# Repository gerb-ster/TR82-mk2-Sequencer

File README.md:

# TR82 mk2 'sequencer'

A 16-step sequencer for the TR82 mk2 drum computer.

## Status: Work in Progress

- done: first schematic & board design
- todo: breadboard and test
- todo: design frontpanel
- todo: order PCB and build prototype

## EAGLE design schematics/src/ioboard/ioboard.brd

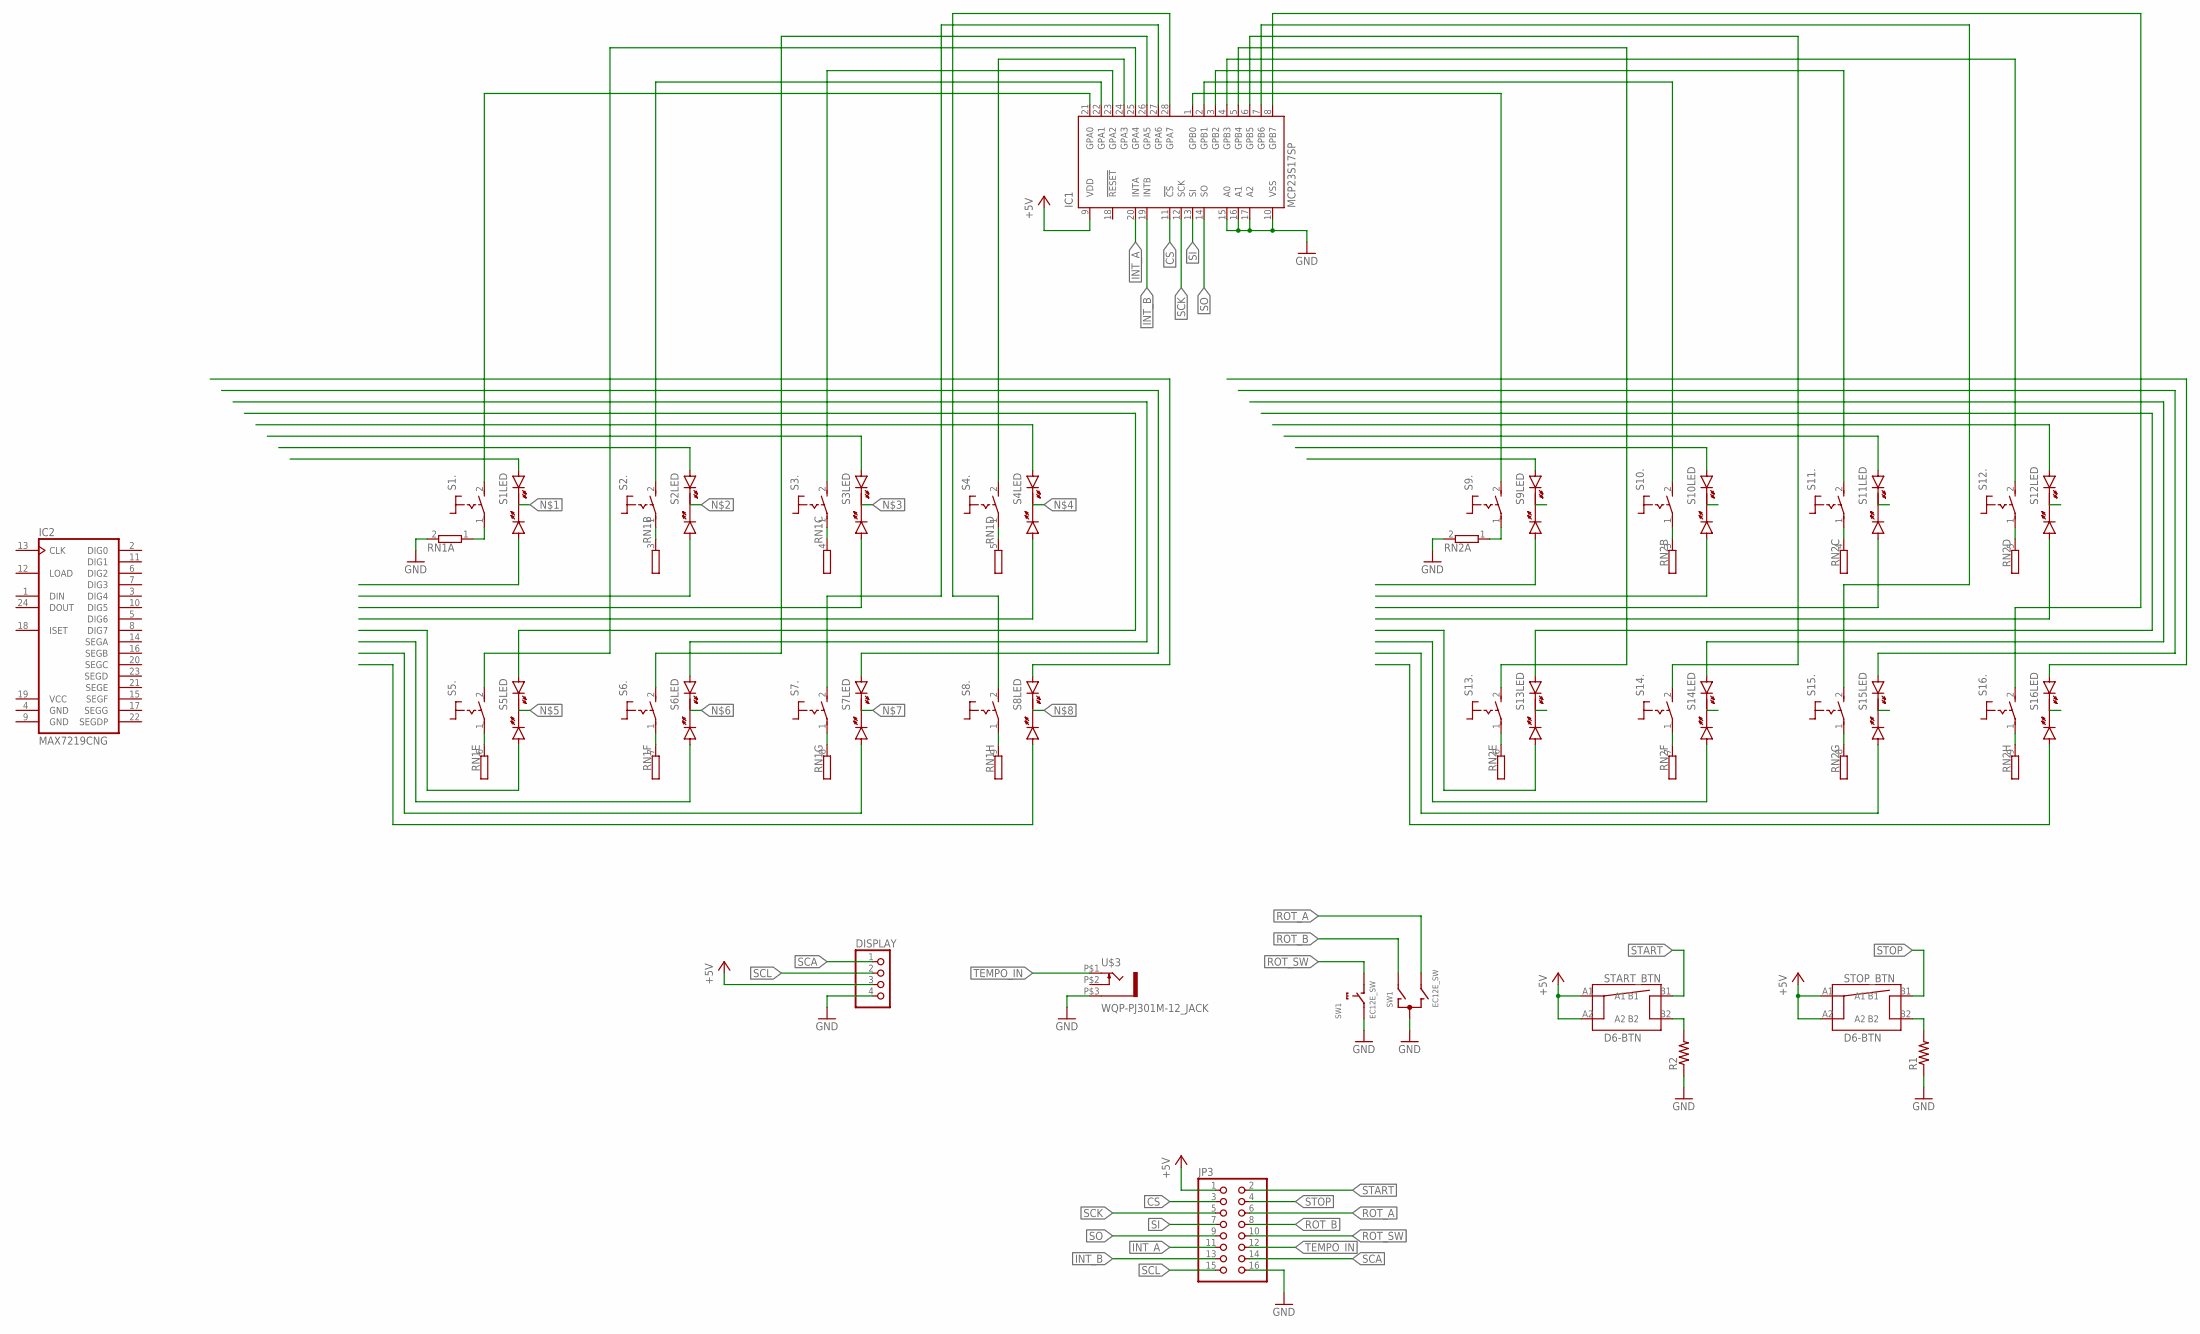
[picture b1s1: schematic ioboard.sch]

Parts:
DISPLAY: PINHD-1X4; 1X04
IC1: MCP23S17SP; DIL28-3
IC2: MAX7219CNG; DIL24-3
JP3: PINHD-2X8; 2X08
R1, R2: R-US_0207/7; 0207/7
RN1, RN2: GE08R; SIL9
S1, S2, S3, S4, S5, S6, S7, S8, S9, S10, S11, S12, S13, S14, S15, S16: MARQ6425-3MM-DUOLED
START_BTN: D6-BTN
STOP_BTN: D6-BTN
SW1: EC12E_SW; ALPS_EC12E_SW
U$3: WQP-PJ301M-12_JACK

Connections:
+5V: DISPLAY.3, IC1.9 (VDD), JP3.1, START_BTN.A1, START_BTN.A2, STOP_BTN.A1, STOP_BTN.A2
CS: IC1.11 (!CS), JP3.3
GND: DISPLAY.4, IC1.10 (VSS), IC1.15 (A0), IC1.16 (A1), IC1.17 (A2), IC2.4 (GND), IC2.9 (GND), JP3.16, R1.1, R2.1, RN1.2, RN2.2, SW1.C, SW1.E (2), U$3.P$3 (1)
INT_A: IC1.20 (INTA), JP3.11
INT_B: IC1.19 (INTB), JP3.13
unnamed: RN1.9 (2), S8.1
unnamed: RN1.8 (2), S7.1
unnamed: RN1.7 (2), S6.1
unnamed: RN1.6 (2), S5.1
unnamed: RN1.5 (2), S4.1
unnamed: RN1.4 (2), S3.1
unnamed: RN1.3 (2), S2.1
unnamed: RN1.1, S1.1
unnamed: RN2.3 (2), S10.1
unnamed: RN2.4 (2), S11.1
unnamed: RN2.5 (2), S12.1
unnamed: RN2.6 (2), S13.1
unnamed: RN2.7 (2), S14.1
unnamed: RN2.8 (2), S15.1
unnamed: RN2.9 (2), S16.1
unnamed: RN2.1, S9.1
unnamed: IC1.21 (GPA0), S1.2 (S)
unnamed: IC1.22 (GPA1), S2.2 (S)
unnamed: IC1.23 (GPA2), S3.2 (S)
unnamed: IC1.24 (GPA3), S4.2 (S)
unnamed: IC1.25 (GPA4), S5.2 (S)
unnamed: IC1.26 (GPA5), S6.2 (S)
unnamed: IC1.27 (GPA6), S7.2 (S)
unnamed: IC1.28 (GPA7), S8.2 (S)
unnamed: IC1.1 (GPB0), S9.2 (S)
unnamed: IC1.2 (GPB1), S10.2 (S)
unnamed: IC1.3 (GPB2), S11.2 (S)
unnamed: IC1.4 (GPB3), S12.2 (S)
unnamed: IC1.5 (GPB4), S13.2 (S)
unnamed: IC1.6 (GPB5), S14.2 (S)
unnamed: IC1.7 (GPB6), S15.2 (S)
unnamed: IC1.8 (GPB7), S16.2 (S)
unnamed: R2.2, START_BTN.B2
unnamed: R1.2, STOP_BTN.B2
ROT_A: JP3.6, SW1.B
ROT_B: JP3.8, SW1.A
ROT_SW: JP3.10, SW1.D (1)
SCA: DISPLAY.1, JP3.14
SCK: IC1.12 (SCK), JP3.5
SCL: DISPLAY.2, JP3.15
SI: IC1.13 (SI), JP3.7
SO: IC1.14 (SO), JP3.9
START: JP3.2, START_BTN.B1
STOP: JP3.4, STOP_BTN.B1
TEMPO_IN: JP3.12, U$3.P$1 (2)
VCC: IC2.19 (VCC)

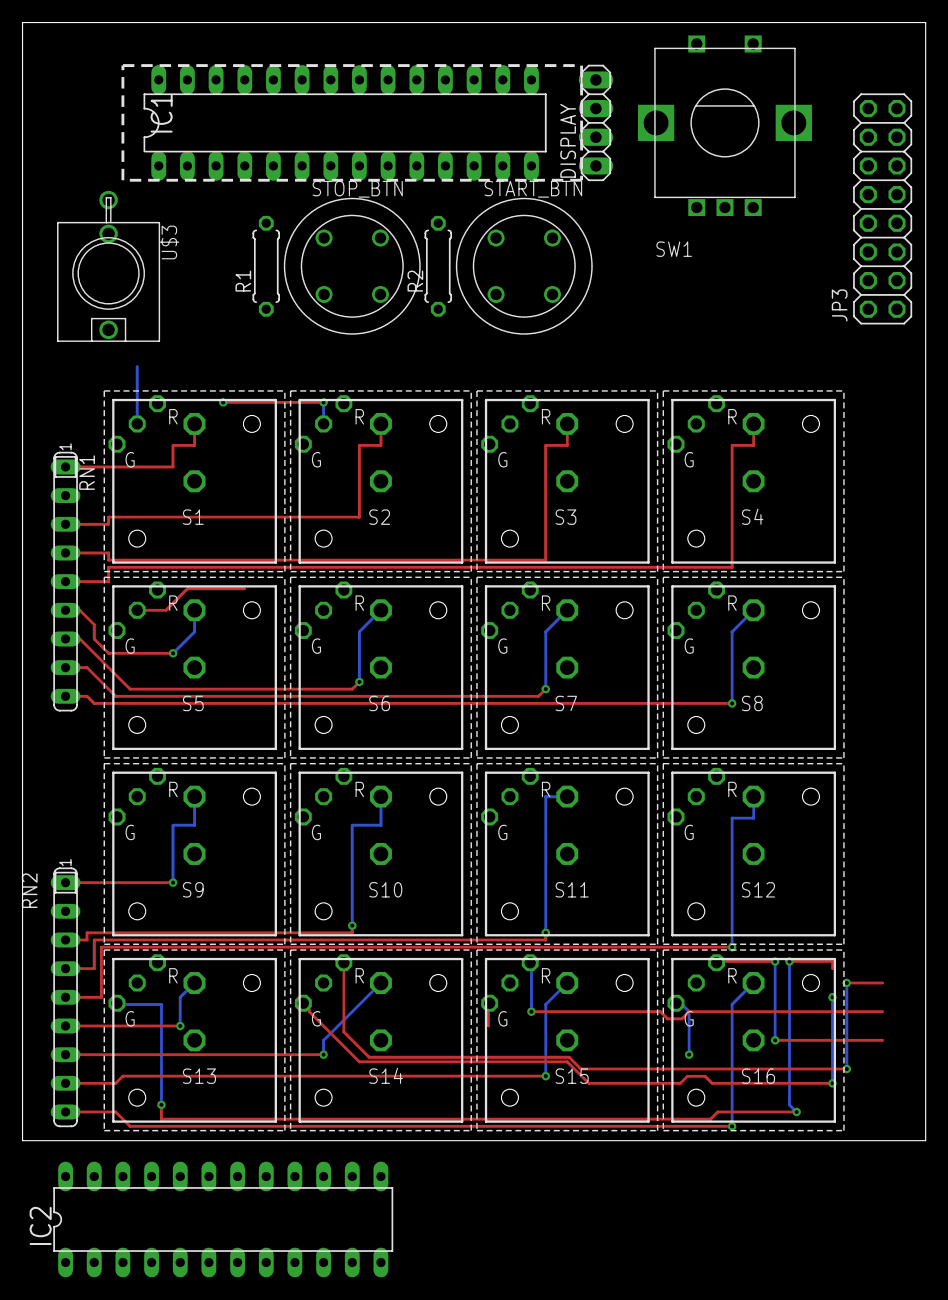
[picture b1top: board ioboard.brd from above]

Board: 2 copper layers, 80.0 x 99.1 mm, 28 parts (0 on the bottom side), 50 nets.

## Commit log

2021-07-19 Fixed minor issues, added documentation and updated some faceplates
2021-08-06 Updated some schematics and docs
2021-08-10 Fixed some bugs and updated documentation
2022-04-20 Some updates & bugfixes
2022-04-22 Fixed schematics & descriptions
2022-05-17 Updated Firmware
2022-05-18 Updated Faceplates
2022-05-18 Fixed issues
2022-05-21 Fixed schematics
2022-05-28 General updates
